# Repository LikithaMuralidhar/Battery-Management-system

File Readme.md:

# Battery Management System for 48V Lithium-Ion Battery Pack

**A comprehensive BMS solution for 48V Li-Ion battery packs with real-time monitoring and protection**

</div>

---

## Table of Contents

- [Overview](#-overview)
- [Features](#-features)
- [Specifications](#-specifications)
- [Hardware Components](#-hardware-components)
- [PCB Design](#-pcb-design)
- [Software Interface](#-software-interface)
- [Installation](#-installation)
- [Usage](#-usage)
- [Results](#-results)
- [Safety](#-safety)
- [Contributing](#-contributing)
- [Acknowledgments](#-acknowledgments)

---

## Overview

This project presents a complete Battery Management System (BMS) designed for 48V Lithium-Ion battery packs. The system provides comprehensive monitoring, protection, and balancing capabilities for applications such as electric vehicles, e-bikes, and energy storage systems.

### Key Highlights

-  13S10P Configuration (130 cells total)
-  Real-time monitoring via JBD Tools software
- Active cell balancing
- Multiple protection mechanisms
- Open-source PCB design using KiCad
- Tested with 1.2kW BLDC Hub Motor

---

## Features

### Protection Systems

| Feature | Description |
|---------|-------------|
| **Overvoltage Protection** | Individual cell and pack monitoring |
| **Undervoltage Protection** | Prevents deep discharge damage |
| **Overcurrent Protection** | Charging (6.5A) and discharging limits |
| **Temperature Monitoring** | Real-time thermal tracking |
| **Cell Balancing** | Automatic balancing (±40mV threshold) |
| **Short Circuit Protection** | Immediate fault detection |
| **MOSFET Control** | Separate charge/discharge management |

### Monitoring Capabilities

- Real-time voltage for all 13 series cells
- Pack voltage measurement
- Bidirectional current sensing
- Temperature monitoring
- State of Charge (SoC) estimation
- Cycle count tracking
- Comprehensive alert system

---

## Specifications

### Battery Pack

```yaml
Voltage: 48V (46.8V nominal)
Configuration: 13S10P (13 series, 10 parallel)
Total Cells: 130 cells
Cell Type: 18650 Lithium-Ion
Cell Voltage: 3.6V nominal
Cell Capacity: 2900mAh (2.9Ah)
Pack Capacity: 29Ah
Total Energy: ~1.4kWh
```

### Load System

```yaml
Motor Type: BLDC Hub Motor
Motor Rating: 48V, 530 RPM, 1.2kW
Charger: 54.2V, 6A
Max Charging Current: 6.35A
Operating Temperature: -20°C to 60°C
```

### Protection Thresholds

| Parameter | Min | Max | Unit |
|-----------|-----|-----|------|
| Cell Voltage | 2.5 | 4.2 | V |
| Pack Voltage | 32.5 | 54.6 | V |
| Charge Current | - | 6.5 | A |
| Discharge Current | - | 30 | A |
| Temperature | -10 | 60 | °C |

---

## Hardware Components

### Main Components

```
├── BMS Protection Board
│   ├── Microcontroller (STM32/ATmega)
│   ├── Voltage Sensing ICs
│   ├── Current Sensors
│   └── UART Communication
│
├── Power Stage
│   ├── Charge MOSFET
│   ├── Discharge MOSFET
│   └── Gate Drivers
│
├── Sensors
│   ├── NTC Thermistors
│   ├── Current Shunt Resistors
│   └── Voltage Divider Networks
│
└── Load System
    ├── BLDC Hub Motor
    ├── Motor Controller
    └── Throttle Interface
```

### Bill of Materials (BOM)

| Component | Quantity | Description |
|-----------|----------|-------------|
| 18650 Li-Ion Cells | 130 | 2900mAh, 3.6V nominal |
| BMS IC | 1 | 13S protection board |
| N-Channel MOSFETs | 2 | Charge/Discharge control |
| Current Sensor | 1 | Hall effect or shunt-based |
| NTC Thermistor | 2-3 | Temperature monitoring |
| Nickel Strips | As needed | For spot welding |
| PCB | 1 | Custom designed |
| Connectors | Various | XT60, JST, etc. |

---

## PCB Design

### Design Tools

**Software:** [KiCad](https://www.kicad.org/) (Open-source EDA)

### Features
- Schematic capture with hierarchical design
- Multi-layer PCB layout
- DRC (Design Rule Check) compliant
- Gerber file generation
- 3D visualization
- SPICE simulation support

### Design Process

```mermaid
graph LR
    A[Schematic Design] --> B[Footprint Assignment]
    B --> C[PCB Layout]
    C --> D[Component Routing]
    D --> E[DRC Check]
    E --> F[Gerber Generation]
    F --> G[Manufacturing]
```

### PCB Specifications

- **Layers:** 2-4 layers
- **Dimensions:** Optimized for battery pack integration
- **Copper Weight:** 2oz for power traces
- **Finish:** HASL or ENIG
- **Files Included:**
  - Gerber files
  - Drill files
  - Pick and place files
  - BOM (Bill of Materials)

---

## Software Interface

### JBD Tools Software

#### Key Features

- **UART Communication** - Standard serial interface
- **Parameter Configuration** - Adjust protection thresholds
- **Real-time Monitoring** - Live data visualization
- **Alert System** - Protection status notifications
- **Data Logging** - Track battery performance

#### Monitored Parameters

```yaml
Cell Voltages: V1-V13 (individual)
Pack Voltage: Total voltage
Current: Charge/Discharge (A)
Temperature: Real-time (°C)
SoC: State of Charge (%)
Capacity: Remaining/Full (mAh)
Cycles: Total charge cycles
Balance Status: ON/OFF per cell
FET Status: Charge/Discharge MOSFET
Alerts: All protection triggers
```

---

## Installation

### Hardware Setup

#### 1. Battery Pack Assembly

```bash
# Materials Required
- 130x 18650 cells (matched capacity)
- Spot welding machine (5kVA recommended)
- Nickel strips (0.15mm thickness)
- Insulation sheets
- Heat shrink wrap
- BMS board
```

**Assembly Steps:**

1. **Cell Testing & Sorting**
   - Test all cells for capacity matching
   - Sort into groups with <50mAh difference
   - Charge all cells to 3.7V

2. **Spot Welding**
   - Create 10P groups using nickel strips
   - Connect 13 groups in series
   - Use proper welding current (50-80A, 0.1-0.2s)

3. **BMS Integration**
   - Connect balance wires (13 connections)
   - Connect main power terminals
   - Install temperature sensors
   - Mount BMS securely on pack

4. **Insulation & Packaging**
   - Apply insulation sheets
   - Wrap with heat shrink
   - Add terminal connectors

#### 2. Software Setup

```bash
# Download JBD Tools
# Available for Windows PC

1. Install JBD Tools software
2. Connect BMS via USB-UART adapter
3. Configure COM port settings
   - Baud rate: 9600
   - Data bits: 8
   - Stop bits: 1
   - Parity: None
```

### Configuration

```python
# Example protection parameters

Cell_OVP = 4.2V      # Overvoltage protection
Cell_UVP = 2.5V      # Undervoltage protection
Pack_OVP = 54.6V     # Pack overvoltage
Pack_UVP = 32.5V     # Pack undervoltage
Charge_OCP = 6.5A    # Charge overcurrent
Discharge_OCP = 30A  # Discharge overcurrent
Balance_Voltage = 40mV  # Balance threshold
Temp_High = 60°C     # High temperature limit
Temp_Low = -10°C     # Low temperature limit
```

---

## 📖 Usage

### Basic Operation

#### Charging

```bash
1. Connect approved charger (54.2V, 6A max)
2. Monitor charging via JBD Tools
3. Charging stops automatically when:
   - Pack voltage reaches 54.6V
   - Any cell reaches 4.2V
   - Current exceeds 6.5A
   - Temperature exceeds limits
```

#### Discharging

```bash
1. Connect load (e.g., BLDC motor)
2. Monitor discharge parameters
3. BMS will disconnect if:
   - Pack voltage < 32.5V
   - Any cell < 2.5V
   - Current exceeds limits
   - Temperature out of range
```

#### Cell Balancing

```bash
# Automatic process
- Activates when cell voltage difference > 40mV
- Balancing current: 50-100mA typical
- Status shown in JBD Tools as "ON"
- Typically occurs near full charge
```

### JBD Tools Interface

#### Main Display

```
┌─────────────────────────────────────────┐
│ Cell Voltages (V)  │  Balance │ Status  │
├─────────────────────────────────────────┤
│ Cell 1:  3.632     │          │  ✓      │
│ Cell 2:  3.631     │          │  ✓      │
│ ...                │          │         │
│ Cell 13: 3.637     │          │  ✓      │
├─────────────────────────────────────────┤
│ Pack Voltage:  47.39V                   │
│ Current:       0.00A                    │
│ Temperature:   24.3°C                   │
│ SoC:           45%                      │
│ Capacity:      12960/29000 mAh         │
│ Cycles:        22                       │
├─────────────────────────────────────────┤
│ Charge FET:    ON    Discharge FET: ON  │
└─────────────────────────────────────────┘
```

---

## 📊 Results

### Performance Validation

#### Test 1: Normal Operation
- **Pack Voltage:** 47.39V
- **Cell Voltage Range:** 3.632V - 3.667V (35mV spread)
- **Temperature:** 24°C
- **Status:** All protection systems operational 

#### Test 2: Charging Process
- **Charging Current:** 6.02A
- **Cell Voltage Range:** 3.693V - 3.737V
- **SoC:** 45% → Charging
- **Protection:** Overcurrent limit enforced at 6.5A 

#### Test 3: Cell Balancing
- **Balance Threshold:** 40mV
- **Active Balancing:** Cells 1, 5, 9 (marked "ON")
- **Pack Voltage:** 51.81V
- **SoC:** 74%
- **Result:** Successful voltage equalization 

#### Test 4: Discharging
- **Discharge Current:** -0.86A (motor at low speed)
- **Cell Voltage Range:** 3.617V - 3.658V
- **Pack Voltage:** 47.26V
- **SoC:** 45%
- **Motor Performance:** Stable operation 

### Key Achievements
 **Prototype Validation** - 4-cell design successfully scaled to 13S10P  
 **MATLAB Simulation** - Circuit analysis confirmed  
 **Protection Systems** - All safety mechanisms functional  
 **Temperature Monitoring** - Real-time tracking operational  
 **MOSFET Control** - Proper switching behavior verified  
 **Load Testing** - 1.2kW motor successfully powered  

---

## Safety

> Improper handling can result in fire, explosion, or injury.
> Always follow safety procedures.

### Safety Guidelines

#### DO:
- Use appropriate safety equipment (goggles, gloves)
- Work in well-ventilated areas
- Keep fire extinguisher nearby (Class D)
- Monitor temperature during operation
- Use manufacturer-approved chargers
- Inspect cells for damage before assembly
- Test BMS functionality before full assembly
- Store at 3.7-3.8V for long-term storage

#### DON'T:
- Exceed rated voltage or current limits
- Short circuit battery terminals
- Puncture or damage cells
- Expose to extreme temperatures
- Use damaged or swollen cells
- Charge unattended
- Bypass protection systems
- Mix cells of different capacities

### Emergency Procedures

```bash
# In case of thermal runaway:
1. Move to safe area away from flammable materials
2. Use Class D fire extinguisher
3. DO NOT use water
4. Evacuate area if fire spreads
5. Call emergency services
```

---

## Troubleshooting

### Common Issues

| Issue | Possible Cause | Solution |
|-------|---------------|----------|
| BMS not communicating | UART connection | Check COM port, baud rate |
| Cells not balancing | Voltage difference < 40mV | Normal, wait until higher SoC |
| Charge FET off | Overvoltage detected | Check cell voltages, reset BMS |
| Discharge FET off | Undervoltage detected | Charge battery pack |
| High temperature | Excessive current | Reduce load, improve cooling |
| SoC inaccurate | Calibration needed | Full charge/discharge cycle |

---

## Contributing

Contributions are welcome! Please follow these guidelines:

### How to Contribute

1. **Fork the repository**
2. **Create a feature branch** (`git checkout -b feature/AmazingFeature`)
3. **Commit changes** (`git commit -m 'Add AmazingFeature'`)
4. **Push to branch** (`git push origin feature/AmazingFeature`)
5. **Open a Pull Request**

### Development Setup

```bash
# Clone repository
git clone https://github.com/yourusername/48v-bms.git

# Navigate to project
cd 48v-bms

# Open KiCad project
kicad bms-48v.kicad_pro
```

### Code of Conduct

- Be respectful and inclusive
- Provide constructive feedback
- Focus on improving the project
- Follow coding standards

---

## 📁 Project Structure

```
48v-bms/
├── hardware/
│   ├── kicad/
│   │   ├── bms-schematic.kicad_sch
│   │   ├── bms-pcb.kicad_pcb
│   │   └── libraries/
│   ├── gerber/
│   │   └── manufacturing_files/
│   └── bom/
│       └── bill_of_materials.csv
│
├── software/
│   ├── jbd-tools/
│   │   └── configuration_files/
│   ├── matlab/
│   │   └── simulation_files/
│   └── firmware/
│       └── (firmware)
│
├── README.md
```

---

## 🎓 Acknowledgments

### Institution
**Department of Electrical and Electronics Engineering**  
**BNM Institute of Technology (BNMIT)**  
Academic Year: 2021-2022

### Special Thanks
- Faculty advisors for guidance and support
- Lab technicians for equipment access
- Fellow students for collaboration
- Open-source community (KiCad, GitHub)

### References
- Battery Management System Design Standards
- IEEE Standards for Battery Testing
- Lithium-Ion Battery Safety Guidelines
- KiCad PCB Design Best Practices

---

## Contact

### Project Maintainers

- **Email:** likithm18ee022@bnmit.edu.in
- **Institution:** BNMIT, Department of EEE

<div align="center">

**Made by BNMIT EEE Department**

[⬆ Back to Top](#-battery-management-system-for-48v-lithium-ion-battery-pack)

</div>

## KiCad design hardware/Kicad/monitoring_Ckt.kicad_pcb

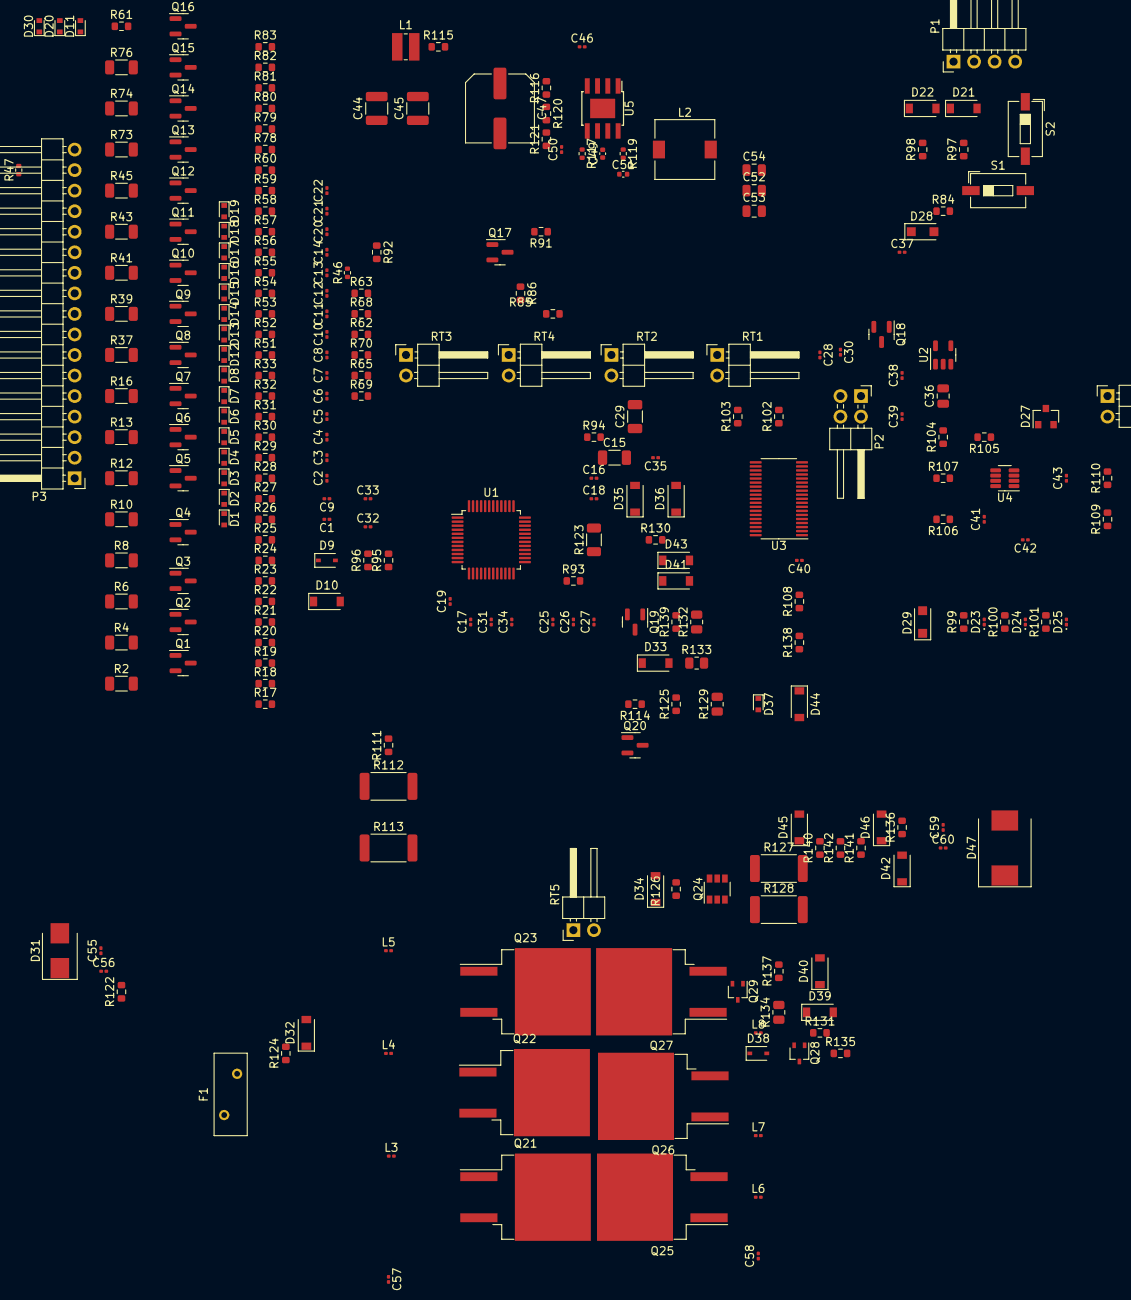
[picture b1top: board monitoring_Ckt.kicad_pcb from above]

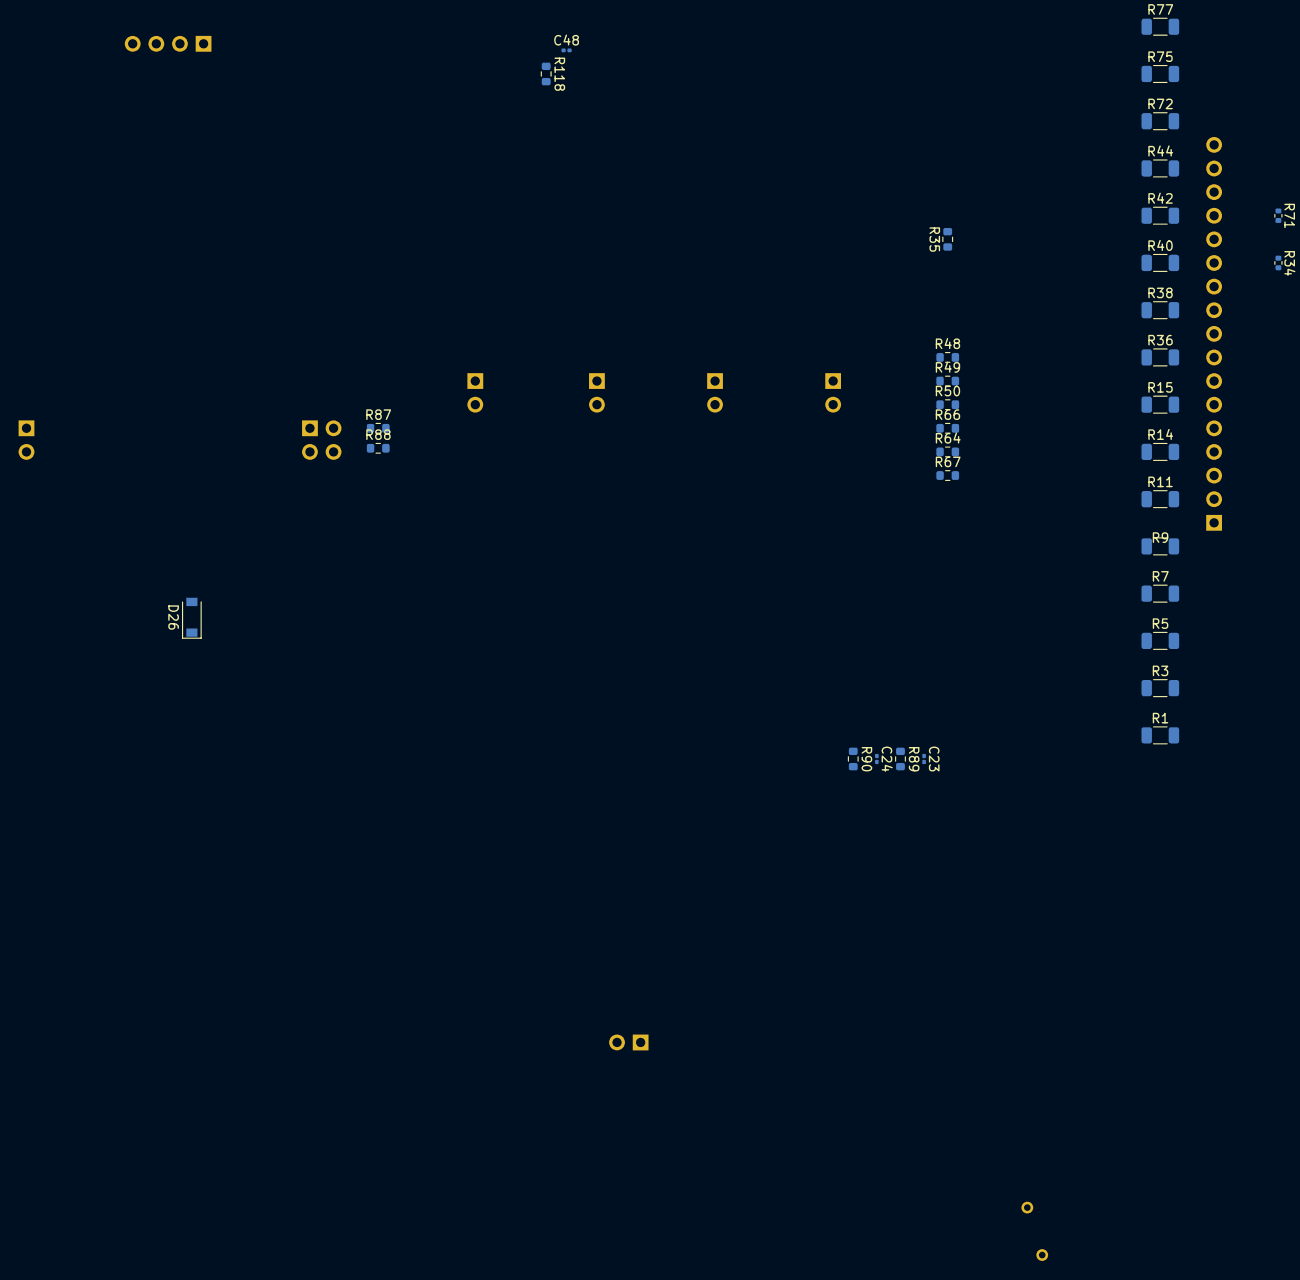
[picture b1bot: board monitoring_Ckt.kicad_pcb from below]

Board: 2 copper layers, 303 parts (34 on the bottom side), 181 nets, no tracks yet.

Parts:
C1, C2, C3, C4, C5, C6, C7, C8, C9, C10, C11, C12, C13, C14, C20, C21, C22: 0.22uf; C_0201_0603Metric
C15: 2.2uF; C_1206_3216Metric
C16, C17, C23, C24, C50: 100pF; C_0201_0603Metric
C18, C25, C26: 1uF; C_0201_0603Metric
C19, C37: 2.2uF; C_0201_0603Metric
C27: 0.022uF; C_0201_0603Metric
C28, C30, C31, C34: 470uF; C_0201_0603Metric
C29: 1uF; C_1206_3216Metric
C32, C38, C41, C42, C43, C46, C55, C56, C57, C58, C59, C60: 0.1uF; C_0201_0603Metric
C33: 100pFD; C_0201_0603Metric
C35: 440pF; C_0201_0603Metric
C36: 10uF; C_0805_2012Metric
C39: 1000pF; C_0201_0603Metric
C40: 470pF; C_0201_0603Metric
C44, C45: 4.7uF; C_1210_3225Metric
C47: 10uF; C_Elec_8x6.2
C48: NC; C_0201_0603Metric
C49: 2200pF; C_0402_1005Metric
C51: 1500pF; C_0402_1005Metric
C52, C53, C54: 4.7uF; C_0805_2012Metric
D1, D2, D3, D4, D5, D6, D7, D8, D12, D13, D14, D15, D16, D17, D18, D19: 5.6V; D_SOD-523
D9: BAT42WS-7-F; D_SOD-323
D10, D21, D22: MMSZ4685T1G 3.6V; D_SOD-123
D11, D20, D30, D37: BAS516,115; D_SOD-523
D23, D24, D25: 150060RS75000; LED_0201_0603Metric
D26: MMSZ4690T1G 5.6V; D_SOD-123
D27: NUP3105LT1G; D_SOT-23_ANK
D28, D29: PMEG2010AEH,115; D_SOD-123F
D31: SMBJ60A-13-F 60V; D_SMB
D32, D34, D39: 16V; D_SOD-123
D33, D41, D43: 75V; D_SOD-123
D35: NC; D_SOD-123
D36, D42, D44, D45, D46: BAT46W-7-F; D_SOD-123
D38: BZT52C5V1S-7-F 5.1V; D_SOD-323
D40: MMSZ5246B-7-F; D_SOD-123
D47: D_SMC
F1: 0678L9300-02; Fuse_BelFuse_0ZRE0016FF_L9.9mm_W3.8mm
L1: 10uH; L_Wuerth_MAPI-3015
L2: 68uH; L_7.3x7.3_H3.5
L3, L4, L5, L8: 600 ohm; L_0201_0603Metric
L6, L7: 600ohm; L_0201_0603Metric
P1: HEADER 4; PinHeader_1x04_P2.54mm_Horizontal
P2: HEADER 2X2; PinHeader_2x02_P2.54mm_Horizontal
P3: HEADER 17; PinHeader_1x17_P2.54mm_Horizontal
P4: HEADER 2; PinHeader_1x02_P2.54mm_Horizontal
Q1, Q2, Q3, Q4, Q5, Q6, Q7, Q8, Q9, Q10, Q11, Q12, Q13, Q14, Q15, Q16: DMG2302UK-7; SOT-23
Q17: ZXMP10A13FTA; SOT-23
Q18: BSS123; SOT-23
Q19: ZXTN25100BFHTA; SOT-23
Q20: DMN10H220L-7; SOT-23
Q21, Q22, Q23, Q25, Q26, Q27: CSD19536KTT; TO-263-2
Q24: FDC3535; SuperSOT-6
Q28: DMG1013UW-7; SOT-323_SC-70
Q29: 2N7002W-7-F; SOT-323_SC-70
R1, R3, R5, R7, R10, R12, R14, R15, R36, R38, R40, R42, R45, R72, R75, R76: CRCW120680R6FKEA; R_1206_3216Metric
R2, R4, R6, R8, R9, R11, R13, R16, R37, R39, R41, R43, R44, R73, R74, R77: 80.6; R_1206_3216Metric
R17, R19, R21, R23, R25, R27, R29, R31, R33, R52, R54, R56, R58, R60, R61, R79, R81, R83, R87, R88, R93, R95, R96, R97, R98, R105, R106, R107, R115, R130: 100; R_0603_1608Metric
R18, R20, R22, R24, R26, R28, R30, R32, R51, R53, R55, R57, R59, R78, R80, R82, R89, R90, R102, R103, R108: 10K; R_0603_1608Metric
R34, R46, R47, R71, R117: 0; R_0402_1005Metric
R35, R48, R49, R50, R62, R63, R64, R65, R66, R67, R68, R69, R70, R111: 0; R_0603_1608Metric
R84, R136: 10k; R_0603_1608Metric
R85: 13.3k; R_0603_1608Metric
R86: 665k; R_0603_1608Metric
R91: 3.3M; R_0603_1608Metric
R92, R126: 1.0M; R_0603_1608Metric
R94: 249; R_0603_1608Metric
R99, R100, R101: 470; R_0603_1608Metric
R104: 47.0k; R_0603_1608Metric
R109, R110: 60.4; R_0603_1608Metric
R112, R113: 0.002; R_2512_6332Metric
R114, R139: 5.1k; R_0603_1608Metric
R116: 82.5k; R_0603_1608Metric
R118: NC; R_0603_1608Metric
R119: 52.3k; R_0402_1005Metric
R120: 63.4K; R_0603_1608Metric
R121: 200K; R_0603_1608Metric
R122: 200; R_0603_1608Metric
R123: 499; R_1206_3216Metric
R124, R131, R137: 10M; R_0603_1608Metric
R125, R138, R140: 49.9k; R_0603_1608Metric
R127, R128: 510; R_2512_6332Metric
R129: 56k; R_0805_2012Metric
R132, R133, R134: 511; R_0805_2012Metric
R135: 511; R_0603_1608Metric
R141, R142: 20k; R_0603_1608Metric
RT1, RT2, RT3: Thermistor_NTC; PinHeader_1x02_P2.54mm_Horizontal
RT4: RT4; PinHeader_1x02_P2.54mm_Horizontal
RT5: TMP6131DECR; PinHeader_1x02_P2.54mm_Horizontal
S1: RS-032G05A3-SM_RT; SW_DIP_SPSTx01_Slide_6.7x4.1mm_W6.73mm_P2.54mm_LowProfile_J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
S2: SW_SPST; SW_DIP_SPSTx01_Slide_6.7x4.1mm_W6.73mm_P2.54mm_LowProfile_J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
U1: BQ76952PFBR; TQFP-48_7x7mm_P0.5mm
U2: TLV70433DBVT; SOT-23-5
U3: MSP430FR2155TDBTR; TSSOP-38_4.4x9.7mm_P0.5mm
U4: TCAN1044VDDFR; SOT-23-8
U5: LM5163DDAR; TI_SO-PowerPAD-8

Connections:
/AUX POWER/POW_EN: U3.18 (P4.5/UCB1CLK), U5.3 (EN/UVLO)
/BAT+: C56.2, D31.1, F1.1
/BAT-: C55.1, D31.2, R96.1, R111.2, R112.1, R113.1
/HIGH SIDE MOSFETS AND DRIVERS/CHG: R123.1, U1.45 (CHG)
/HIGH SIDE MOSFETS AND DRIVERS/Fuse: D29.1, Q20.1, R114.2
/HIGH SIDE MOSFETS AND DRIVERS/PDSG: D33.1, R125.1, U1.39 (PDSG)
/MCU and Communication/3V3: C36.1, C38.1, C42.1, P1.4, R102.1, R103.1, R104.2, U2.3 (OUT), U3.10 (DVCC), U4.5 (VIO)
/MCU and Communication/5V: C37.2, C41.1, C51.2, C52.1, C53.1, C54.1, D26.1, D28.1, L2.2, R121.1, U2.2 (IN), U2.4 (NC_1), U4.3 (VCC)
/MCU and Communication/ALERT: U1.25 (ALERT), U3.20 (P4.3/UCA1TXD/UCA1SIMO/~UCA1TXD)
/MCU and Communication/BATS_EN: Q18.1, U3.19 (P4.4/UCB1STE)
/MCU and Communication/BAT_ADC: C35.1, R85.1, R86.1, U3.28 (P1.7/UCA0TXD/UCA0SIMO/TB0.2/TDO/A7/VREF+)
/MCU and Communication/CANH: D27.1 (K), P4.1, R110.2, U4.7 (CANH)
/MCU and Communication/CANL: D27.2 (K), P4.2, R109.1, U4.6 (CANL)
/MCU and Communication/DCSG: U1.31 (DCHG), U3.22 (P4.1/UCA1CLK)
/MCU and Communication/DDSG: U1.32 (DDSG), U3.23 (P4.0/UCA1STE/ISOTXD/ISORXD)
/MCU and Communication/FETOFF: C23.2, R89.2, U1.30 (DFETOFF), U3.21 (P4.2/UCA1RXD/UCA1SOMI/~UCA1RXD)
/MCU and Communication/FUSE_MCU: D29.2, U3.7 (P1.0/UCB0STE/SMCLK/COMP0.0/A0/VEREF+)
/MCU and Communication/LED1: D23.1, U3.6 (P1.1/UCB0CLK/ACLK/COMP0.1/A1)
/MCU and Communication/LED2: D24.1, U3.5 (P1.2/UCB0SIMO/UCB0SDA/TB0TRG/A2/VEREF-)
/MCU and Communication/LED3: D25.1, U3.4 (P1.3/UCB0SOMI/UCB0SCL/A3)
/MCU and Communication/PTC_PULL: R108.1, U3.38 (P3.3)
/MCU and Communication/RXD: R106.1, U3.1 (P3.2)
/MCU and Communication/SBCLK: R97.2, U3.8 (TEST/SBWTCK)
/MCU and Communication/SBIO: C39.2, R98.2, R104.1, S2.1 (A), U3.9 (RST/NMI/SBWTDIO)
/MCU and Communication/SCL: P2.1, R87.2, R103.2
/MCU and Communication/SCL_MCU: P2.2, U3.16 (P4.7/UCB1SOMI/UCB1SCL)
/MCU and Communication/SDA: P2.3, R88.2, R102.2
/MCU and Communication/SDA_MCU: P2.4, U3.17 (P4.6/UCB1SIMO/UCB1SDA)
/MCU and Communication/SHUT: C24.2, R90.2, U1.33 (RST_SHUT), U3.24 (P2.3/TB1TRG)
/MCU and Communication/STB: R105.2, U3.3 (P3.0/MCLK)
/MCU and Communication/TXD: R107.1, U3.2 (P3.1)
/Monitor and Cell Balancing/5V_AFE: C25.1, D28.2, U1.34 (REG2)
/Monitor and Cell Balancing/CELL 0: D1.2, Q1.2, R17.1
/Monitor and Cell Balancing/CELL 1: D2.2, Q2.2, R1.1, R2.1, R19.1
/Monitor and Cell Balancing/CELL 2: D3.2, Q3.2, R3.1, R4.1, R21.1
/Monitor and Cell Balancing/CELL 3: D4.2, Q4.2, R5.1, R6.1, R23.1
/Monitor and Cell Balancing/CELL 4: D5.2, Q5.2, R7.1, R8.1, R25.1
/Monitor and Cell Balancing/CELL 5: D6.2, Q6.2, R9.1, R10.1, R27.1
/Monitor and Cell Balancing/CELL 6: D7.2, Q7.2, R11.1, R12.1, R29.1
/Monitor and Cell Balancing/CELL 7: D8.2, Q8.2, R13.1, R14.1, R31.1
/Monitor and Cell Balancing/CELL 8: D12.2, Q9.2, R15.1, R16.1, R33.1
/Monitor and Cell Balancing/CELL 9: D13.2, P3.10, Q10.2, R36.1, R37.1, R52.1
/Monitor and Cell Balancing/CELL 10: D14.2, P3.11, Q11.2, R38.1, R39.1, R47.2, R54.1
/Monitor and Cell Balancing/CELL 11: D15.2, P3.12, Q12.2, R40.1, R41.1, R56.1
/Monitor and Cell Balancing/CELL 12: D16.2, P3.13, Q13.2, R34.1, R42.1, R43.1, R58.1
/Monitor and Cell Balancing/CELL 13: D17.2, P3.14, Q14.2, R34.2, R44.1, R45.1, R60.1
/Monitor and Cell Balancing/CELL 14: D18.2, P3.15, Q15.2, R71.2, R72.1, R73.1, R79.1
/Monitor and Cell Balancing/CELL 15: D19.2, P3.16, Q16.2, R71.1, R74.1, R75.1, R81.1
/Monitor and Cell Balancing/CELL 16: D11.2 (A), D20.2 (A), D30.2 (A), P3.17, Q17.2 (S), R47.1, R76.1, R77.1, R83.1, R92.2
/Monitor and Cell Balancing/DSG: D35.1, R130.1, U1.43 (DSG)
/Monitor and Cell Balancing/FUSE_AFE: R114.1, U1.38 (FUSE)
/Monitor and Cell Balancing/LD: D41.1, D44.2, R138.1, U1.41 (LD)
/Monitor and Cell Balancing/PACK: D43.1, R139.1, U1.42 (PACK)
/Monitor and Cell Balancing/SRN: C32.1, C33.1, R95.2, U1.20 (SRN)
/Monitor and Cell Balancing/SRP: C32.2, C33.2, R96.2, U1.18 (SRP)
/Monitor and Cell Balancing/TS1: C28.2, RT1.1, U1.21 (TS1)
/Monitor and Cell Balancing/TS2: C30.1, RT2.2, U1.23 (TS3)
/Monitor and Cell Balancing/TS3: C31.1, RT3.2, U1.28 (HDQ)
/Monitor and Cell Balancing/TS4: C34.1, RT4.2, U1.29 (CFETOFF)
/Monitor and Cell Balancing/VC0: C1.2, D9.1, D10.1, R17.2, R18.2, U1.16 (VC0)
/Monitor and Cell Balancing/VC1: C2.1, C9.2, R19.2, R20.2, U1.15 (VC1)
/Monitor and Cell Balancing/VC2: C2.2, C3.1, R21.2, R22.2, U1.14 (VC2)
/Monitor and Cell Balancing/VC3: C3.2, C4.1, R23.2, R24.2, U1.13 (VC3)
/Monitor and Cell Balancing/VC4: C4.2, C5.1, R25.2, R26.2, U1.12 (VC4)
/Monitor and Cell Balancing/VC5: C5.2, C6.1, R27.2, R28.2, R67.1, R69.2
/Monitor and Cell Balancing/VC6: C6.2, C7.1, R29.2, R30.2, R64.1, R65.2
/Monitor and Cell Balancing/VC7: C7.2, C8.1, R31.2, R32.2, R66.1, R70.2
/Monitor and Cell Balancing/VC8: C8.2, C10.1, R33.2, R50.1, R51.2, R62.2
/Monitor and Cell Balancing/VC9: C10.2, C11.1, R49.1, R52.2, R53.2, R68.2
/Monitor and Cell Balancing/VC10: C11.2, C12.1, R48.1, R54.2, R55.2, R63.2
/Monitor and Cell Balancing/VC11: C12.2, C13.1, R56.2, R57.2, U1.5 (VC11)
/Monitor and Cell Balancing/VC12: C13.2, C14.1, R46.1, R50.2, R58.2, R59.2, U1.4 (VC12)
/Monitor and Cell Balancing/VC13: C14.2, C20.1, R46.2, R60.2, R78.2, U1.3 (VC13)
/Monitor and Cell Balancing/VC14: C20.2, R35.1, R49.2, R79.2, U1.2 (VC14)
/Monitor and Cell Balancing/VC15: C21.2, C22.1, R35.2, R81.2, R82.2, U1.1 (VC15)
/Monitor and Cell Balancing/VC16: C22.2, R48.2, R83.2, U1.48 (VC16)
/Monitor and Cell Balancing/WAKE: C17.2, R84.1, U1.22 (TS2)
/PACK+: C58.2, C60.2, D39.2, D40.2, D47.1, Q25.3, Q26.3, Q27.3, Q29.2 (S), R127.2, R128.2, R131.2, R135.2, R137.2, R140.2, R141.2, R142.2
/PACK-: C59.1, D45.2, D46.2, D47.2, R95.1, R112.2, R113.2, R136.1
GND: C1.1, C9.1, C15.2, C16.2, C17.1, C19.1, C23.1, C24.1, C25.2, C26.2, C27.1, C28.1, C29.1, C30.2, C31.2, C34.2, C35.2, C36.2, C37.1, C38.2, C39.1, C40.2, C41.2, C42.2, C43.2, C44.1, C45.1, C46.1, C47.2, C48.2, C52.2, C53.2, C54.2, D9.2, D10.2, D21.2, D22.2, D26.2, D33.2, D35.2, D36.2, D41.2, D43.2, P1.1, Q18.2, Q20.2, R85.2, R89.1, R90.1, R99.1, R100.1, R101.1, R111.1, R116.1, R120.1, RT1.2, RT2.1, RT3.1, RT4.1, RT5.2 (+), S1.2 (A), S2.2 (B), U1.17 (VSS), U2.1 (GND), U2.5 (NC_2), U3.11 (DVSS), U4.2 (GND), U5.1 (GND), U5.9 (PAD)
unnamed: C15.1, C16.1, C18.1, R61.2, U1.47 (BAT)
unnamed: C18.2, U1.46 (CP1)
unnamed: C19.2, U1.24 (REG18)
unnamed: C21.1, R80.2
unnamed: C26.1, U1.35 (REG1)
unnamed: C27.2, Q19.2 (E), U1.36 (REGIN)
unnamed: C29.2, Q19.3 (C), R94.1
unnamed: C40.1, R108.2, RT5.1 (-), U3.36 (P5.1/TB2.2/MFM.TX/A9)
unnamed: C43.1, R109.2, R110.1
unnamed: C44.2, D30.1 (K), L1.1
unnamed: C45.2, L1.2, R115.1
unnamed: C46.2, C47.1, R115.2, U5.2 (VIN)
unnamed: C48.1, R118.1
unnamed: C49.1, L2.1, R118.2, R119.1, U5.8 (SW)
unnamed: C49.2, R117.2
unnamed: C50.1, R120.2, R121.2, U5.5 (FB)
unnamed: C50.2, C51.1, R119.2
unnamed: C55.2, C56.1
unnamed: C57.1, D32.2, F1.2, Q21.3, Q22.3, Q23.3, R122.1, R124.2
unnamed: C57.2, C58.1
unnamed: C59.2, C60.1
unnamed: D1.1, Q1.1, R18.1
unnamed: D2.1, Q2.1, R20.1
unnamed: D3.1, Q3.1, R22.1
unnamed: D4.1, Q4.1, R24.1
unnamed: D5.1, Q5.1, R26.1
unnamed: D6.1, Q6.1, R28.1
unnamed: D7.1, Q7.1, R30.1
unnamed: D8.1, Q8.1, R32.1
unnamed: D11.1 (K), R61.1
unnamed: D12.1, Q9.1, R51.1
unnamed: D13.1, Q10.1, R53.1
unnamed: D14.1, Q11.1, R55.1
unnamed: D15.1, Q12.1, R57.1
unnamed: D16.1, Q13.1, R59.1
unnamed: D17.1, Q14.1, R78.1
unnamed: D18.1, Q15.1, R80.1
unnamed: D19.1, Q16.1, R82.1
unnamed: D20.1 (K), R94.2
unnamed: D21.1, P1.2, R97.1
unnamed: D22.1, P1.3, R98.1
unnamed: D23.2, R99.2
unnamed: D24.2, R100.2
unnamed: D25.2, R101.2
unnamed: D32.1, L3.1, L4.1, L5.1, R123.2, R124.1
unnamed: D34.1, Q21.2, Q22.2, Q23.2, Q24.4 (S), Q25.2, Q26.2, Q27.2, R126.1
unnamed: D34.2, Q24.3 (G), R125.2, R126.2
unnamed: D36.1, R130.2, R132.1
unnamed: D37.1 (K), D38.2, Q28.1, R129.2
unnamed: D37.2 (A), R129.1, R133.2
unnamed: D38.1, D39.1, L6.2, L7.2, L8.2, Q28.2, R131.1, R134.1
unnamed: D40.1, D42.1, Q29.1 (G), R137.1
unnamed: D42.2, R136.2
unnamed: D44.1, D46.1, R138.2, R141.1, R142.1
unnamed: D45.1, R139.2, R140.1
unnamed: L3.2, Q21.1
unnamed: L4.2, Q22.1
unnamed: L5.2, Q23.1
unnamed: L6.1, Q25.1
unnamed: L7.1, Q26.1
unnamed: L8.1, Q27.1
unnamed: Q1.3, R1.2, R2.2
unnamed: Q2.3, R3.2, R4.2
unnamed: Q3.3, R5.2, R6.2
unnamed: Q4.3, R7.2, R8.2
unnamed: Q5.3, R9.2, R10.2
unnamed: Q6.3, R11.2, R12.2
unnamed: Q7.3, R13.2, R14.2
unnamed: Q8.3, R15.2, R16.2
unnamed: Q9.3, R36.2, R37.2
unnamed: Q10.3, R38.2, R39.2
unnamed: Q11.3, R40.2, R41.2
unnamed: Q12.3, R42.2, R43.2
unnamed: Q13.3, R44.2, R45.2
unnamed: Q14.3, R72.2, R73.2
unnamed: Q15.3, R74.2, R75.2
unnamed: Q16.3, R76.2, R77.2
unnamed: Q17.1 (G), R91.2, R92.1
unnamed: Q17.3 (D), R86.2
unnamed: Q18.3, R91.1
unnamed: Q19.1 (B), R93.2
unnamed: Q20.3, R122.2
unnamed: Q24.1 (D_1), Q24.2 (D_2), Q24.5 (D_3), Q24.6 (D_4), R127.1, R128.1
unnamed: Q28.3, R135.1
unnamed: Q29.3 (D), R134.2
unnamed: R62.1, R64.2, U1.8 (VC8)
unnamed: R63.1, R66.2, U1.6 (VC10)
unnamed: R65.1, R67.2, U1.10 (VC6)
unnamed: R68.1, U1.7 (VC9)
unnamed: R69.1, U1.11 (VC5)
unnamed: R70.1, U1.9 (VC7)
unnamed: R84.2, S1.1 (K)
unnamed: R87.1, U1.26 (SCL)
unnamed: R88.1, U1.27 (SDA)
unnamed: R93.1, U1.37 (BREG)
unnamed: R105.1, U4.8 (STB)
unnamed: R106.2, U4.4 (RXD)
unnamed: R107.2, U4.1 (TXD)
unnamed: R116.2, U5.4 (RON)
unnamed: R117.1, U5.7 (BST)
unnamed: R132.2, R133.1

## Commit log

2025-12-11 Add BQ76952 initialization and read functions
    Implement BQ76952 battery management functions
2025-12-11 Add BQ76952 header file with definitions and prototypes
2025-12-11 Add MSP430 BMS communication and data handling
2025-12-11 Add README for Battery Management System project
    Added comprehensive documentation for the Battery Management System project, including project overview, specifications, features, hardware components, design processes, testing, and safety notes.
2025-12-11 Remove documentation and license sections
    Removed documentation and license sections from the README.
2025-12-11 Update project maintainer's email address
2025-12-11 Refactor README formatting and content
    Updated formatting and removed unnecessary emojis in the README.
2025-12-11 Update Readme by removing project status
    Removed project status section and updated footer.
2025-12-11 Rename MSP430.c to Firmware/MSP430.c
